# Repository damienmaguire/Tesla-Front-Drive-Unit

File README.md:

# Tesla-Front-Drive-Unit
Open Source Logic board to control the Tesla Model S Front Drive Unit
This board replaces the Tesla OEM control board in the high efficency front drive unit
and enables full control of the inverter and motor using simple analog / digital and CAN communication. Design files in DesignSpark 8 format.

Software may be downladed here:
https://github.com/jsphuebner/stm32-sine/releases

Fully built and tested boards and bare PCBs available here : http://www.evbmw.com/index.php/evbmw-webshop

Support forum : https://openinverter.org/forum/

23/09/17 : Released V1 schematic for the logic board. Untested. Also released pinout for the logic to igbt board interface header and Autocad dxf of the board outline with critical component locations.

02/10/17 : Released V1 design files. Untested. Unproven. Educational use only.

06/11/17 : V1 board bench tested and working well. No in car testing as yet.

29/12/17 : Uploaded V2 design files for small drive unit logic board. Compatible with both front and rear small Tesla drive units.

Just one change :

ULN2003 replaced by NCV8401ADT for driving precharge relay and main contactor following in car testing of the large drive unit.

Happy new year :)

14/08/18 : Following some excellent testing and investigation by a european customer, V3 design files are released. Small changes to component values in the current sensor opamp circuit as well as addition of two filter capacitors in the same. Now running well in vehicle. Also uploaded working parameter file.

18/10/18 : Two customers reported failures of their inverter when using the V2 board. One customer reported they had fixed the issue but then refused to share the details. I have worked with the second customer in Romania on the problems. Here are some details :

Root cause of the drive unit inverter failures discovered and fixed.
NOT caused by overcurrent through the igbts but rather the combination of using 8.8kHz switching frequency through a very low inductance stator and the sudden release of the main contactor on an overcurrent detection. The small drive unit inverter works perfectly at 17.6khz switching frequency and setting tripmode to prechon ensures the pre charge resistor can provide a path back to the battery during release of the main contactor. This was tested to the Nth degree on my recent trip to Romania

Working on a fix for a hardware bug that is limiting power. The tesla current sensors span +/- 1250A over a range of 0-5v with 2.5v representing 0A. Seems Tesla use the EXACT SAME hardware overcurrent detection circuit on their logic board as designed by Johannes. They set trip points at .1V and 4.9V giving a total span of 1200A. (1A=2mV). The component choice in the opamp circuit on the open source board causes a hardware overcurrent event at +850A regardless of settings above this value thus limiting power. It was this trip coupled with the above issues relating to main contactor control and switching frequency that lead to inverter deaths.

Identified the hall effect current sensor used in the small drive units as the MLX91209. So at least now if I wreck one they only cost 3 Euros to replace. A V4 design will be released shortly along with details on how to modify the V2 and V3 boards to avoid this problem. 

28/10/18 : V4 Design files released. Major changes : 

Updated current sensor opamp component values to allow the full +/-1200A swing.

Deleted the encoder polarity jumper as no longer needed.

Added option to fit ESP WiFi module on board (untested)

Added jumper to disable RS232 Transciever (required if using on board wifi)

Latest sourcecode and binaries will available from https://github.com/jsphuebner/stm32-sine

V2 and V3 boards can still be used by changing the following component values : R44,R49 = 62k, R48 = 3k16.

On the web interface set the following two parameters :

PWMFRQ=17.6kHz

Tripmode = Prechon

Working and tested full parameter files will be released shortly.

29/10/18 : V2 Design files and BOM updated for modifications and also incorrect values for temp sensor load resistors in BOM.

Test run with modification : https://www.youtube.com/watch?v=mhGwcPWCbsA

21/01/20 : V6 design files now released. Both fully built and partial built boards available from the EVBMW webshop : https://www.evbmw.com/index.php/evbmw-webshop
Don't want to buy from me and support ongoing development? That's ok as this release also includes the BOM, CPL and Gerber files needed to build your own at JLCPCB : https://jlcpcb.com

16/12/25 : Added current Kicad 9 project to redesign the SDU board. Work in progress.

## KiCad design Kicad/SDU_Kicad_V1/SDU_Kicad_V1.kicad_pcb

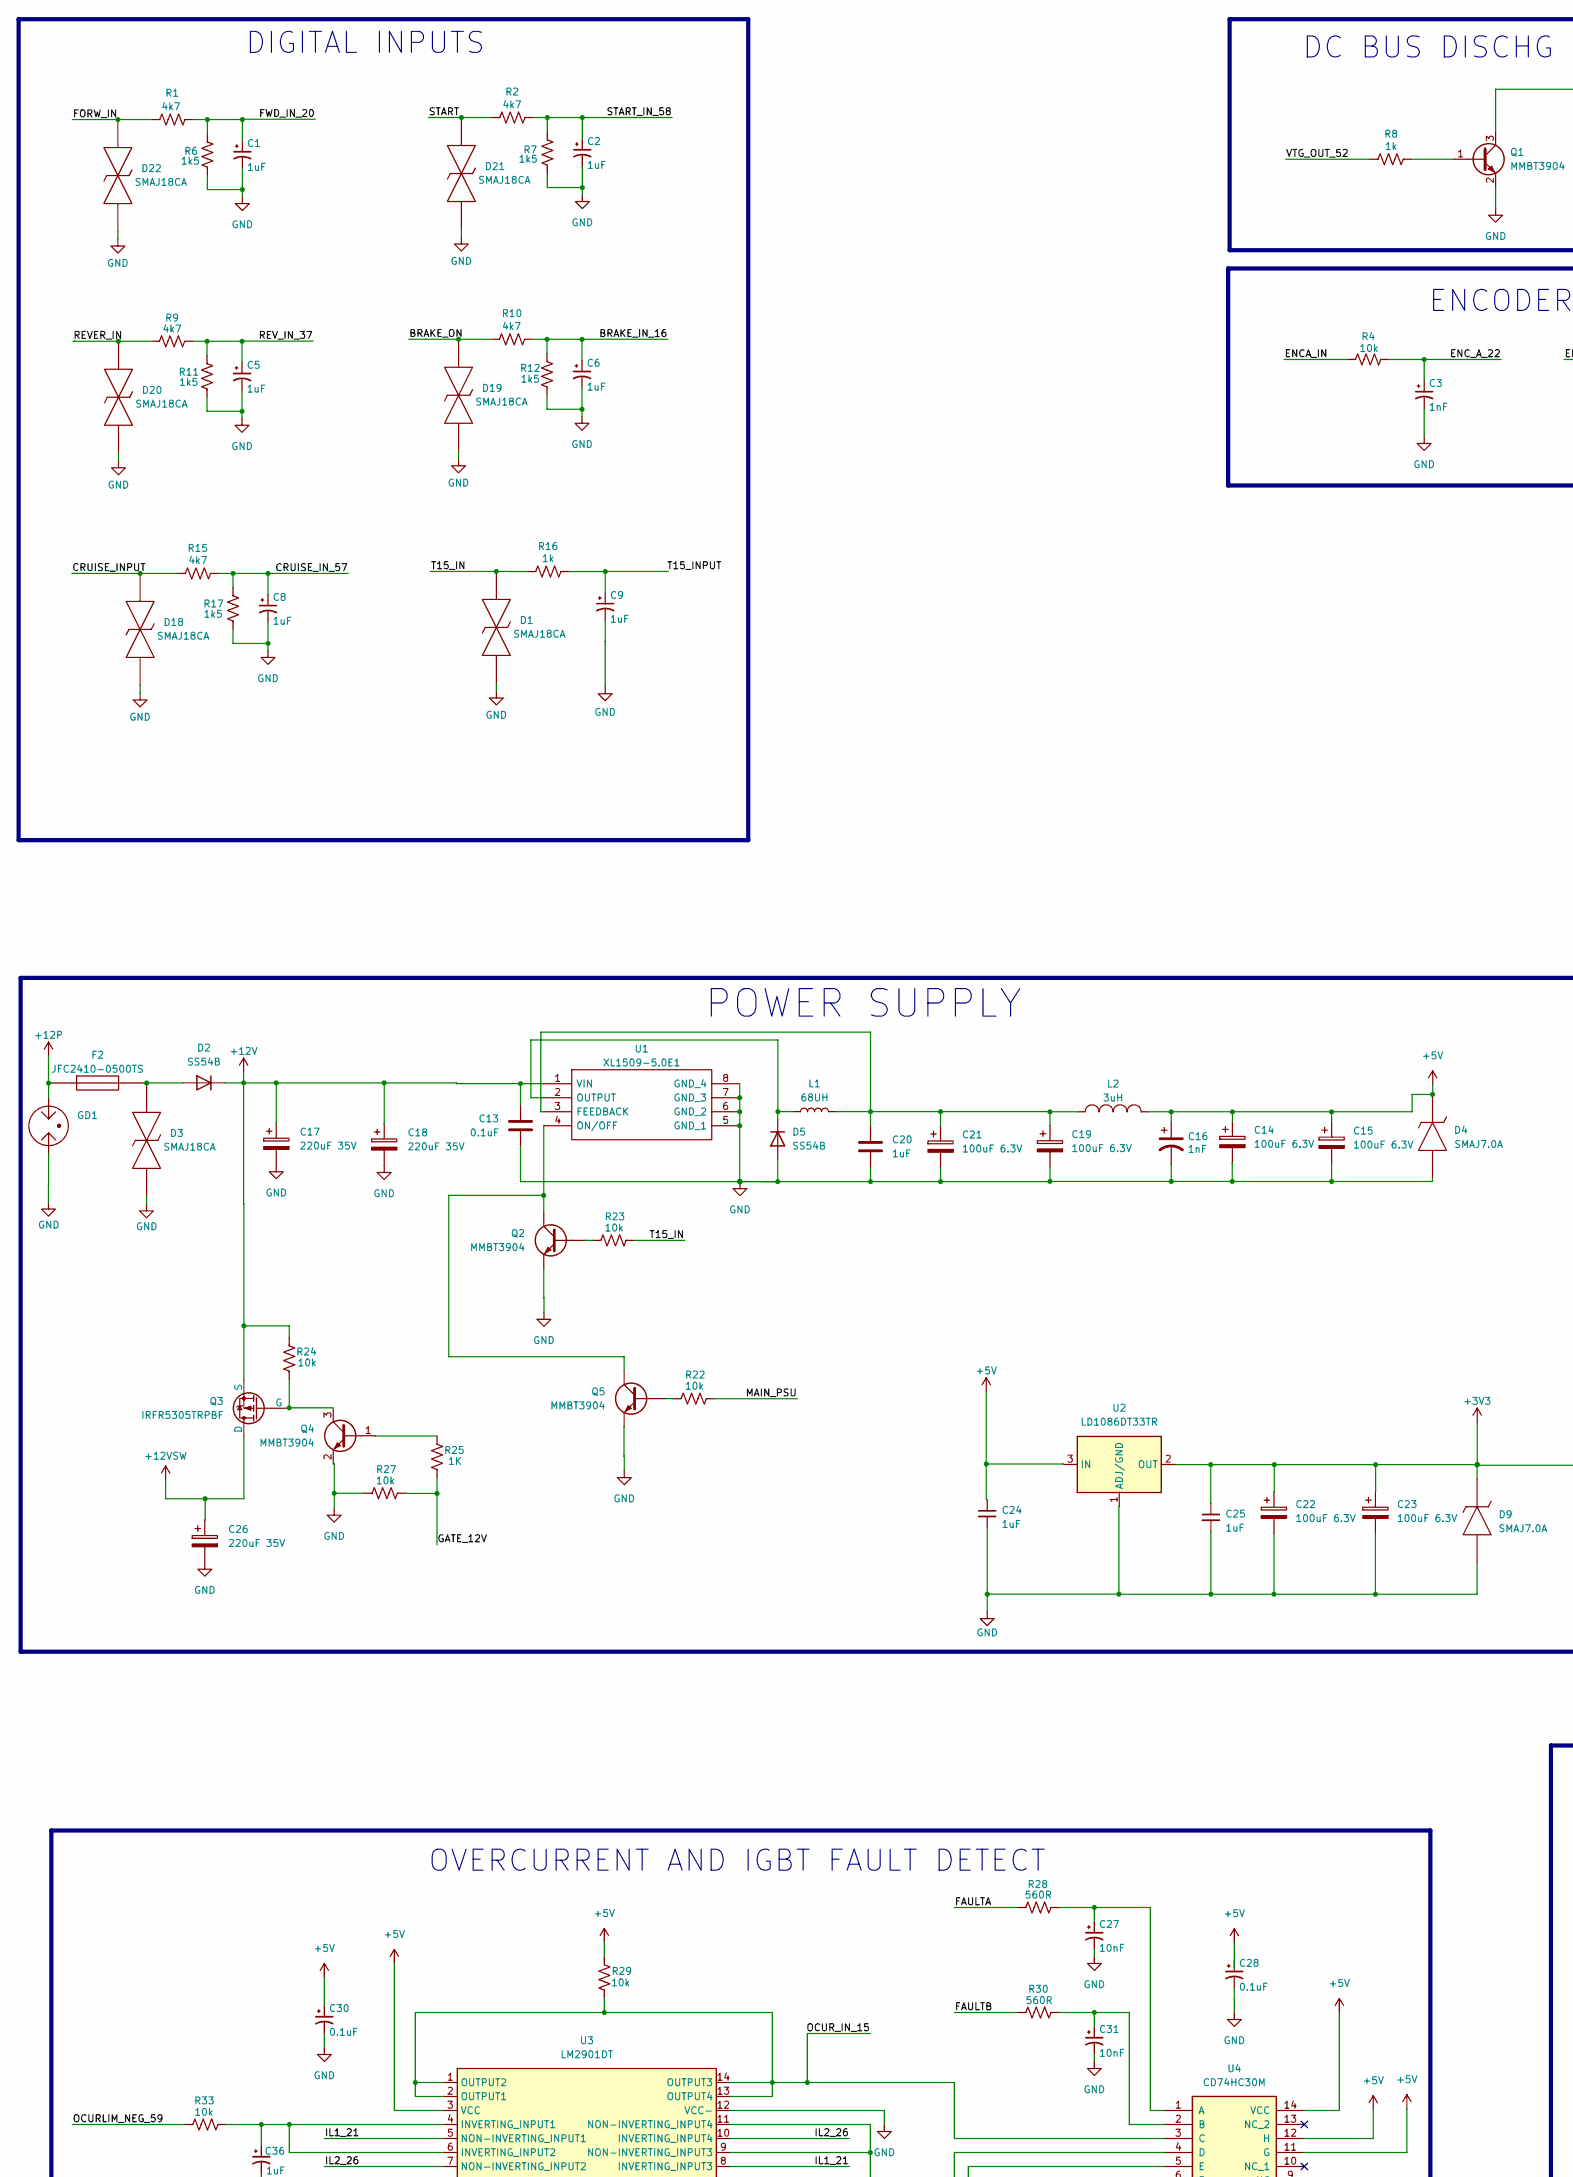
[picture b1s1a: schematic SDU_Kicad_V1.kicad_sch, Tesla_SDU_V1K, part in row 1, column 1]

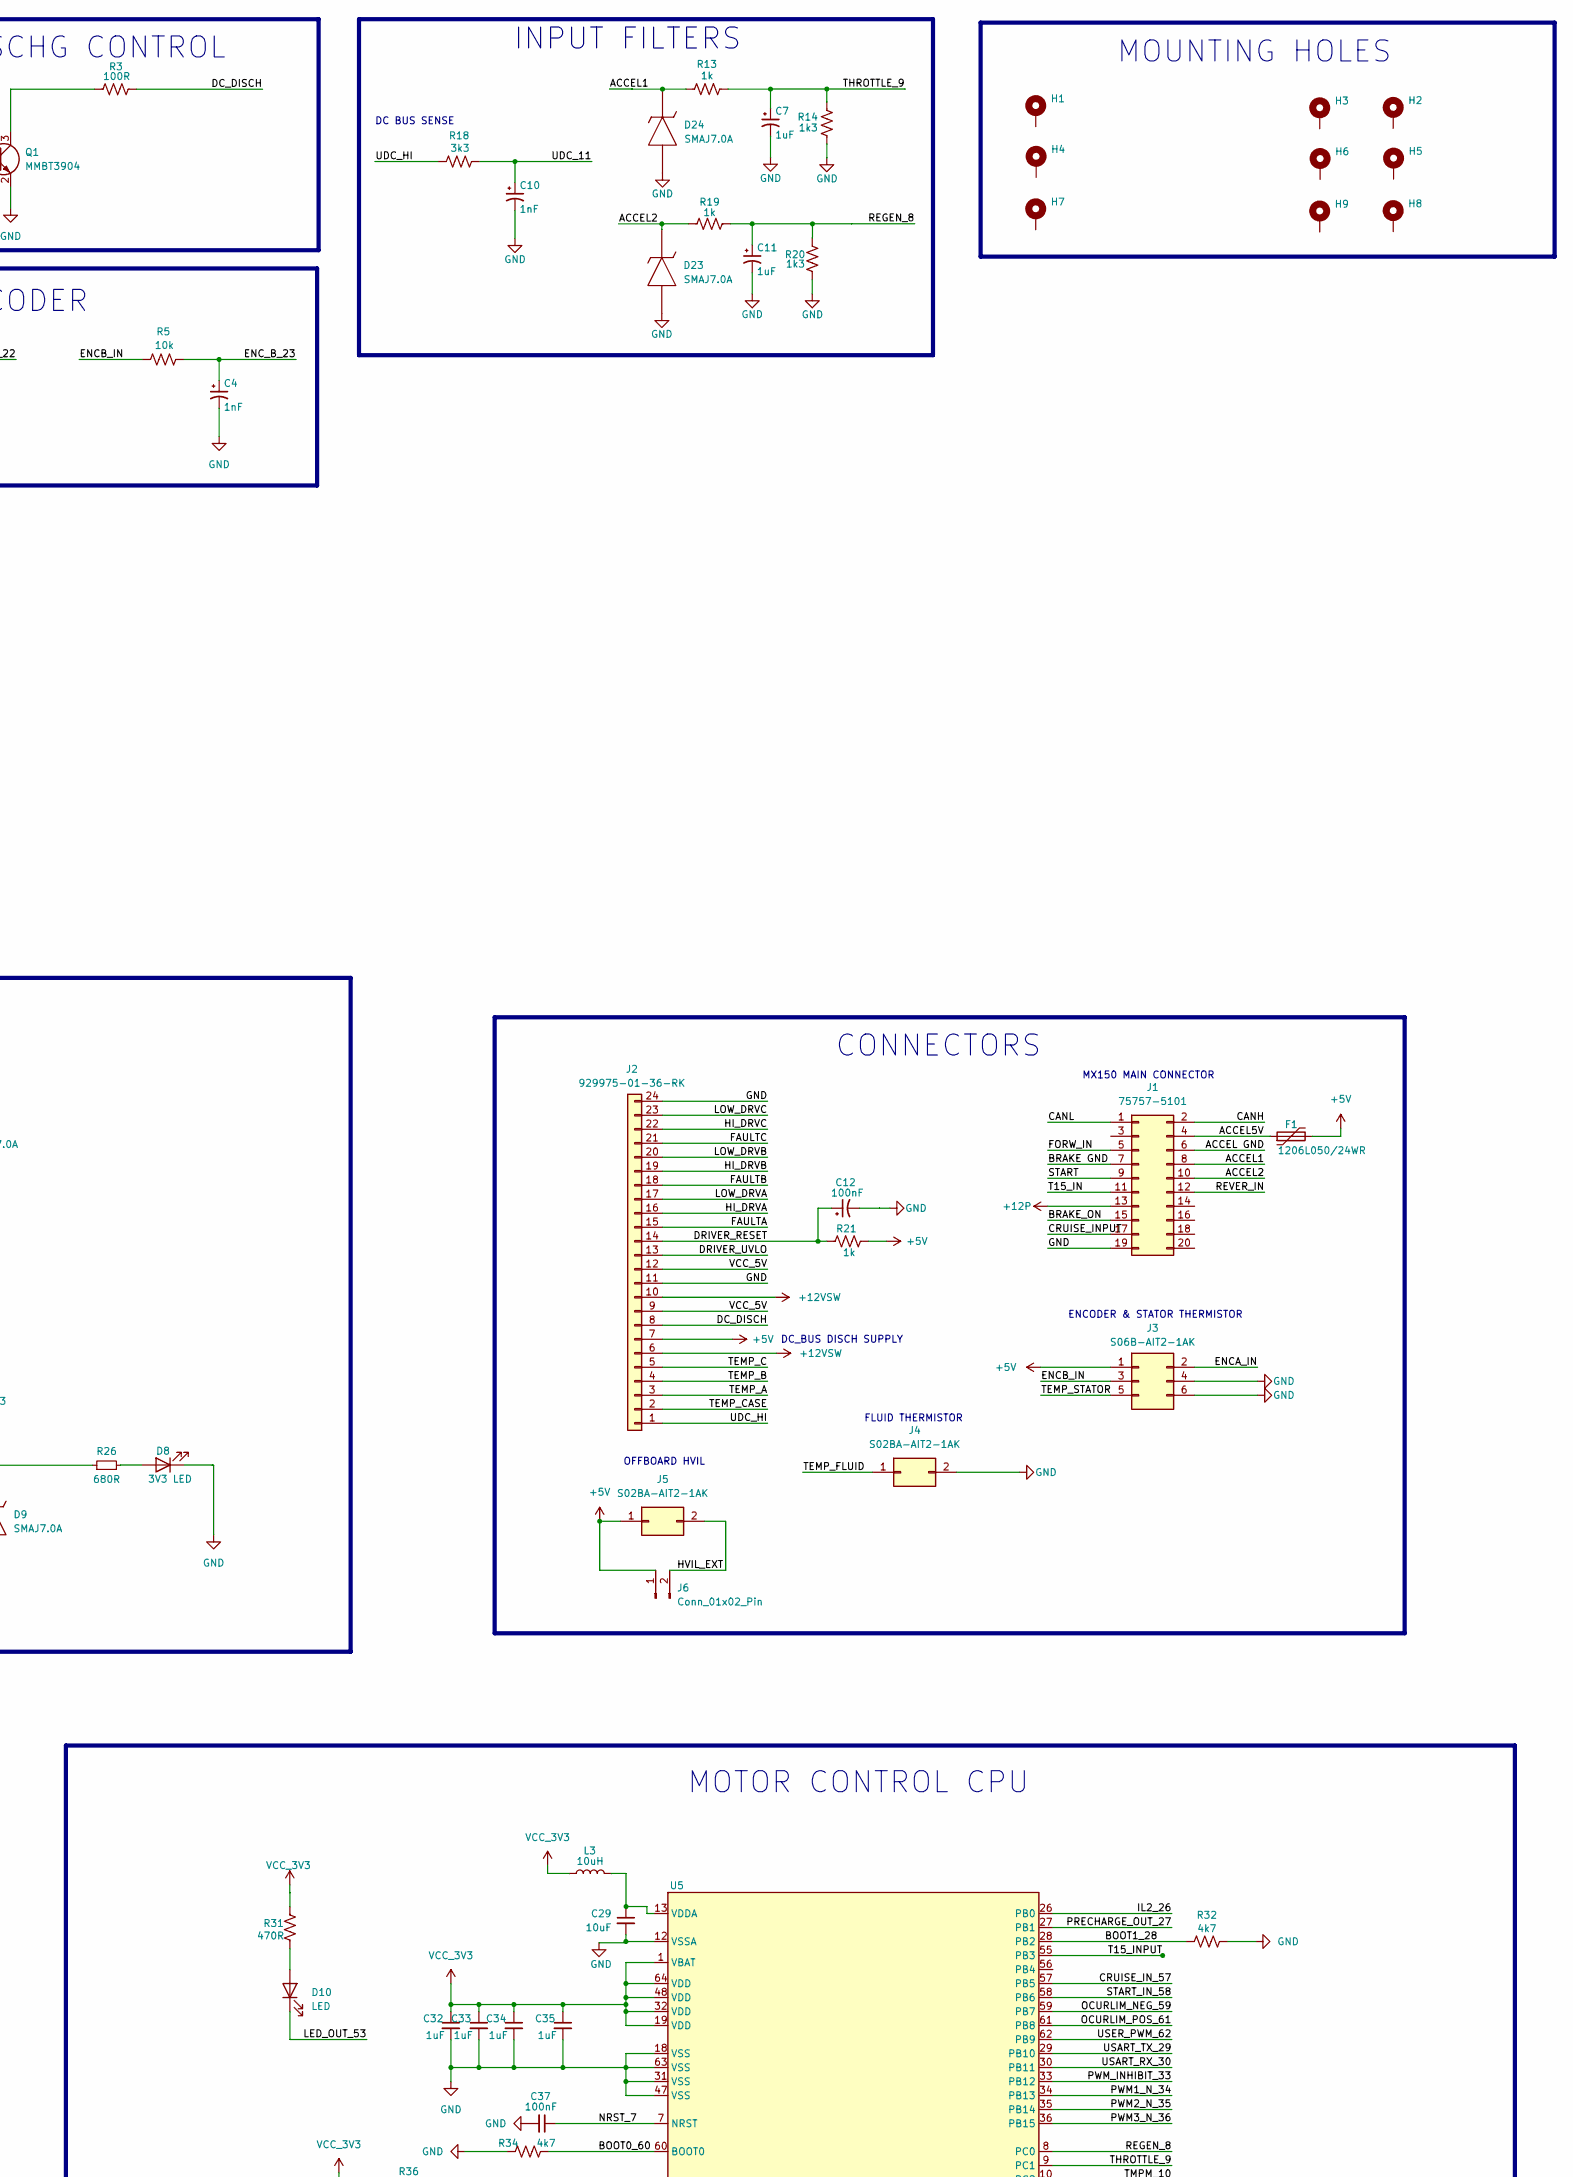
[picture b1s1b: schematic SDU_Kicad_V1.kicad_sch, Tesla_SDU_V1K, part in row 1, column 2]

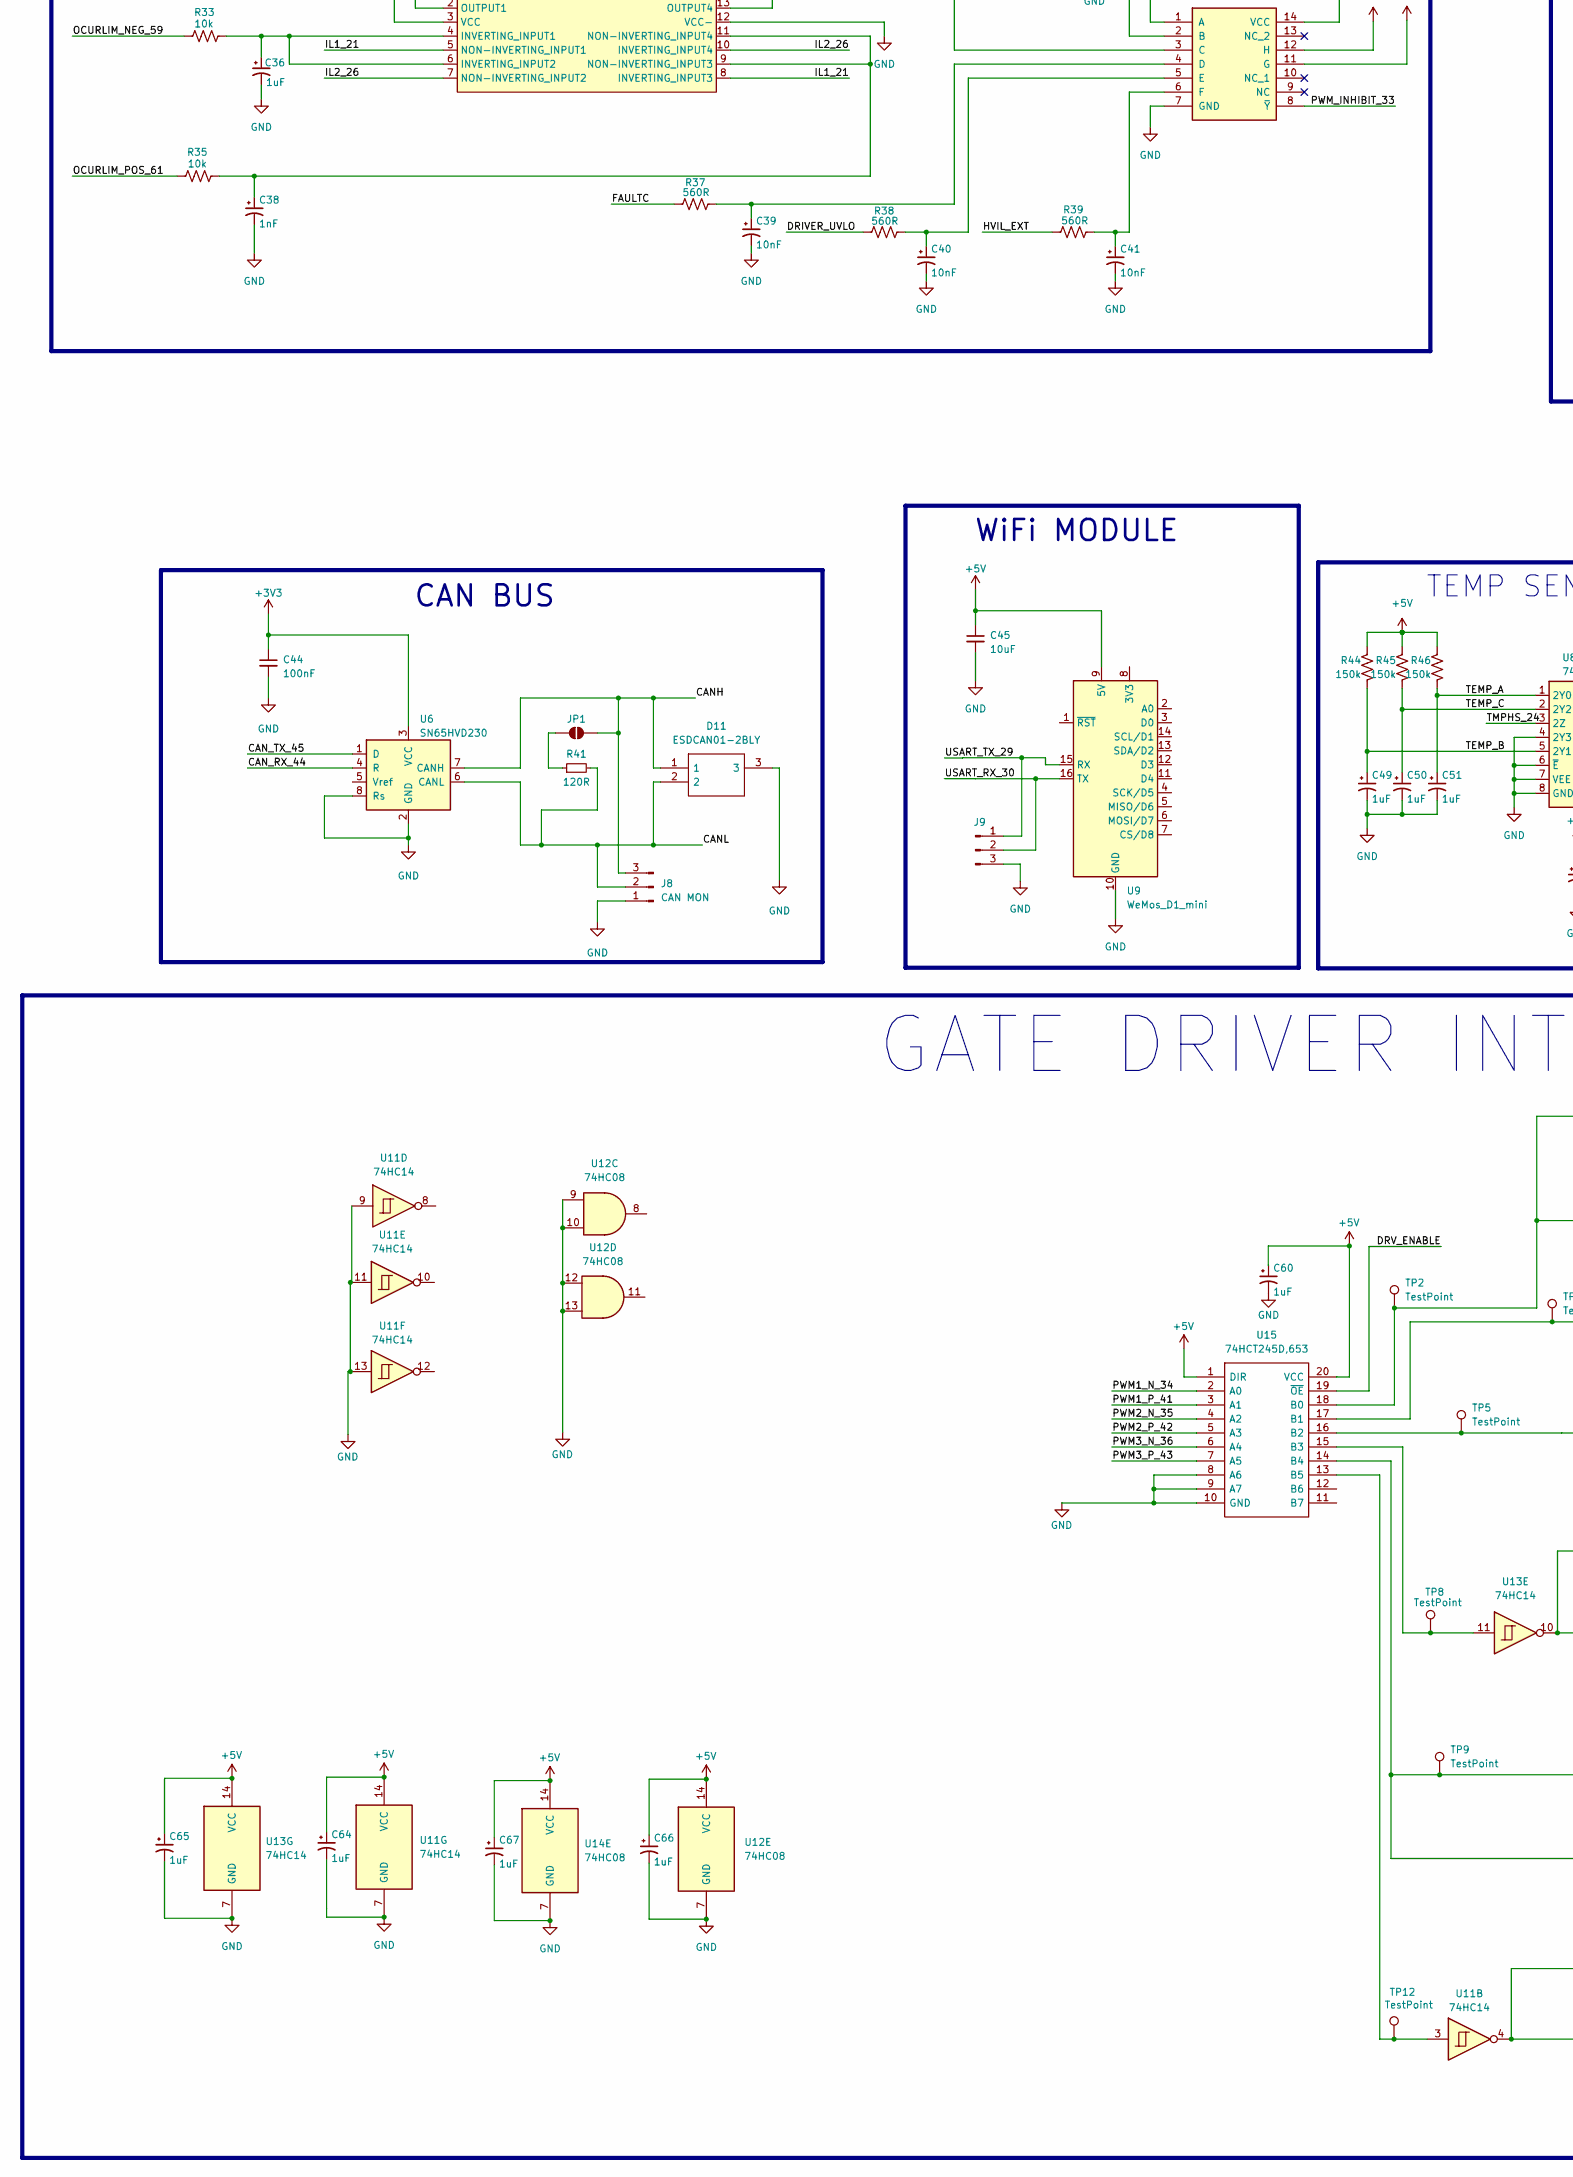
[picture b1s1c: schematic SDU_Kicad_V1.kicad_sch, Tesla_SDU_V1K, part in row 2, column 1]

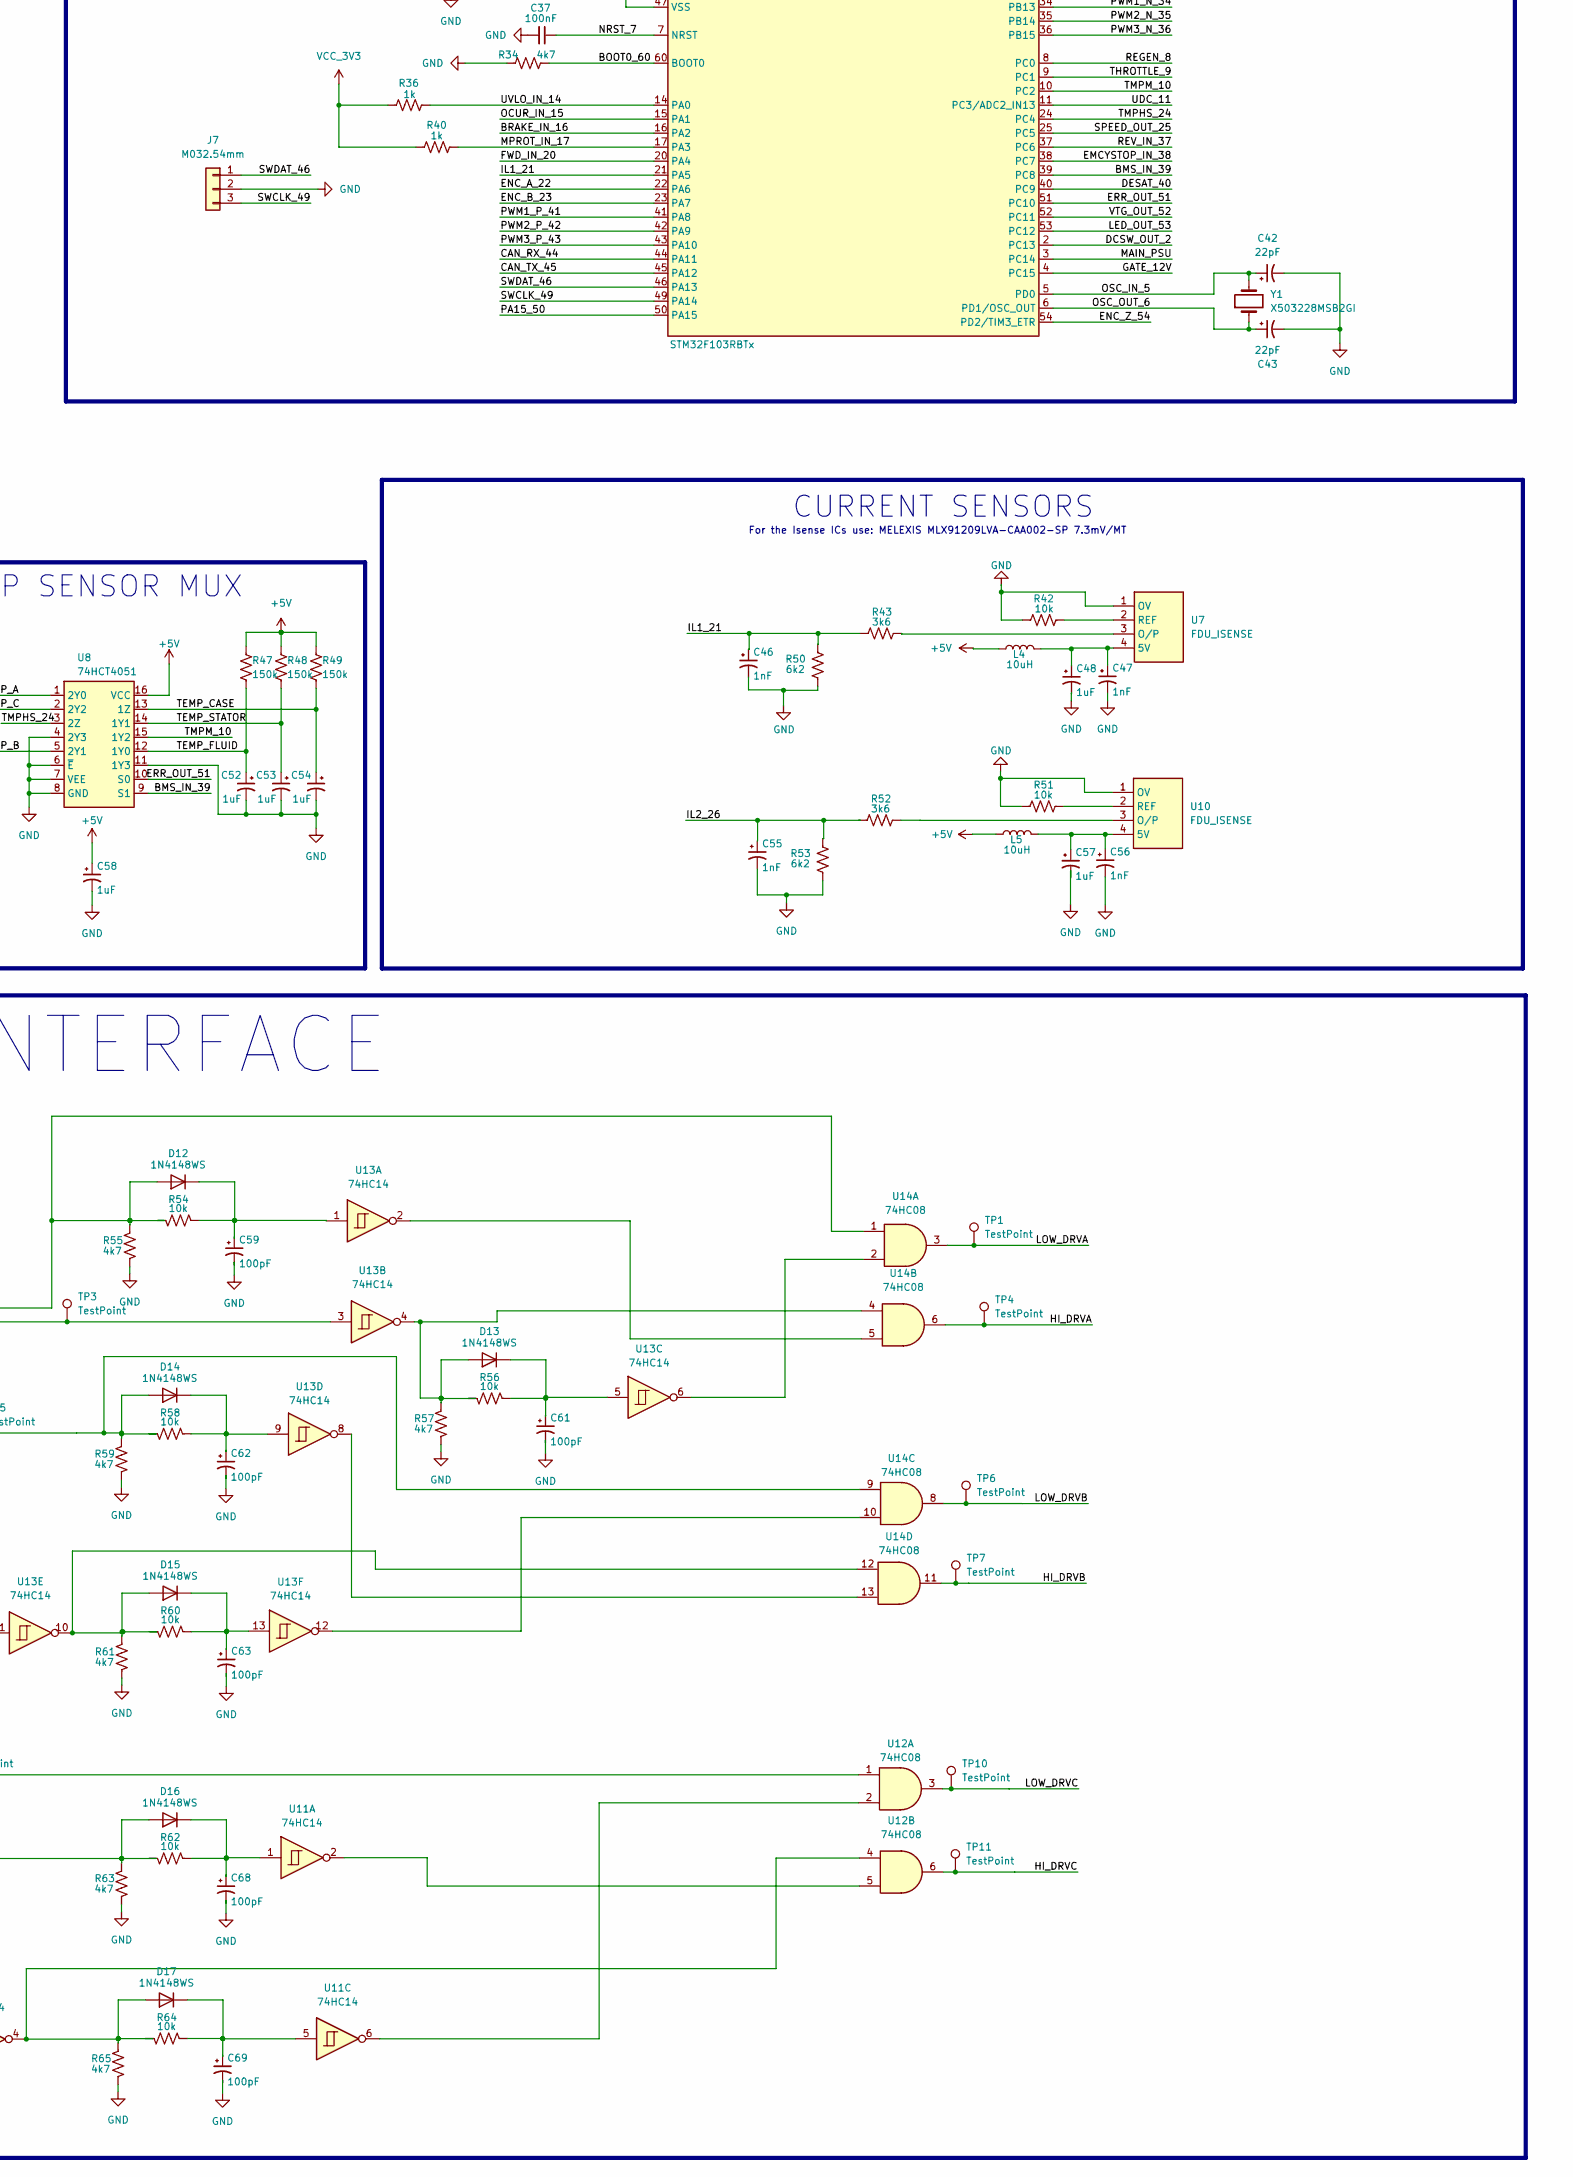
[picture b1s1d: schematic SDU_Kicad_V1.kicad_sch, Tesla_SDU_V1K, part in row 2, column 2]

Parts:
C1, C2, C5, C6, C7, C8, C9, C11, C20, C24, C25, C32, C33, C34, C35, C36, C48, C49, C50, C51, C52, C53, C54, C57, C58, C60, C64, C65, C66, C67: 1uF; C_0805_2012Metric
C3, C4, C10, C16, C38, C46, C47, C55, C56: 1nF; C_0805_2012Metric
C12, C37, C44: 100nF; C_0805_2012Metric
C13, C28, C30: 0.1uF; C_0805_2012Metric
C14, C15, C19, C21, C22, C23: 100uF 6.3V; CP_EIA-3528-15_AVX-H
C17, C18, C26: 220uF 35V; CP_Elec_10x10
C27, C31, C39, C40, C41: 10nF; C_0805_2012Metric
C29, C45: 10uF; C_0805_2012Metric
C42, C43: 22pF; C_0805_2012Metric
C59, C61, C62, C63, C68, C69: 100pF; C_0805_2012Metric
D1, D3, D18, D19, D20, D21, D22: SMAJ18CA; DIONM5127X229N; Manufacturer_Part_Number SMAJ18CA; Mouser Part Number 652-SMAJ18CA
D2, D5: SS54B; D_SMA
D4, D9: SMAJ7.0A; DIOM5026X229N; Manufacturer_Part_Number SMAJ7.0A; Mouser Part Number 576-SMAJ7.0A
D8: 3V3 LED; LED_0805_2012Metric
D10: LED; LED_0805_2012Metric
D11: ESDCAN01-2BLY; SOT95P255X150-3N; Manufacturer_Part_Number ESDCAN01-2BLY; Mouser Part Number 511-ESDCAN01-2BLY
D12, D13, D14, D15, D16, D17: 1N4148WS; D_SOD-323
D23, D24: SMAJ7.0A; DIONM5127X229N; Manufacturer_Part_Number SMAJ7.0A; Mouser Part Number 576-SMAJ7.0A
F1: 1206L050/24WR; Fuse_1206_3216Metric
F2: JFC2410-0500TS; FUSC6126X280N; Manufacturer_Part_Number JFC2410-0500TS
GD1: 2051-09-SM-RPLF; DIOM5336X244N
H1, H4, H7: MountingHole_Pad; MountingHole_5.3mm_M5_Pad_Via
H2, H3, H5, H6, H8, H9: MountingHole_Pad; MountingHole_3.2mm_M3_Pad_Via
J1: 75757-5101; SDU_Conn
J2: 929975-01-36-RK; SDU_IGBT_Conn
J3: S06B-AIT2-1AK; 6pin_JST
J4, J5: S02BA-AIT2-1AK; 2pin_JST
J6: Conn_01x02_Pin; PinHeader_2x01_P2.54mm_Horizontal
J7: M032.54mm; PinSocket_1x03_P2.54mm_Vertical
J8: CAN MON; PinHeader_1x03_P2.54mm_Vertical
J9: Conn_01x03_Pin; PinHeader_1x03_P2.54mm_Vertical
JP1: SolderJumper_2_Open; SolderJumper-2_P1.3mm_Open_Pad1.0x1.5mm
L1: 68UH; L_Sumida_CDMC6D28_7.25x6.5mm
L2: 3uH; L_APV_ANR6020
L3, L4, L5: 10uH; L_0805_2012Metric
Q1, Q2, Q4, Q5: MMBT3904; SOT-23
Q3: IRFR5305TRPBF; TO-252-2
R1, R2, R9, R10, R15, R32, R34, R55, R57, R59, R61, R63, R65: 4k7; R_0805_2012Metric
R3: 100R; R_0805_2012Metric
R4, R5, R22, R23, R24, R27, R29, R33, R35, R42, R51, R54, R56, R58, R60, R62, R64: 10k; R_0805_2012Metric
R6, R7, R11, R12, R17: 1k5; R_0805_2012Metric
R8, R13, R16, R19, R21, R36, R40: 1k; R_0805_2012Metric
R14, R20: 1k3; R_0805_2012Metric
R18: 3k3; R_0805_2012Metric
R25: 1K; R_0805_2012Metric
R26: 680R; R_0805_2012Metric
R28, R30, R37, R38, R39: 560R; R_0805_2012Metric
R31: 470R; R_0805_2012Metric
R41: 120R; R_0805_2012Metric
R43, R52: 3k6; R_0805_2012Metric
R44, R45, R46, R47, R48, R49: 150k; R_0805_2012Metric
R50, R53: 6k2; R_0805_2012Metric
TP1, TP2, TP3, TP4, TP5, TP6, TP7, TP8, TP9, TP10, TP11, TP12: TestPoint; TestPoint_Pad_2.5x2.5mm
U1: XL1509-5.0E1; SOIC127P600X175-8N; Manufacturer_Part_Number XL1509-5.0E1
U2: LD1086DT33TR; TO-252-2
U3: LM2901DT; SOIC-14_3.9x8.7mm_P1.27mm
U4: CD74HC30M; SOIC-14_3.9x8.7mm_P1.27mm
U5: STM32F103RBTx; LQFP-64_10x10mm_P0.5mm
U6: SN65HVD230; SOIC-8_3.9x4.9mm_P1.27mm
U7, U10: FDU_ISENSE; SDU_Isens
U8: 74HCT4051; SOIC-16_3.9x9.9mm_P1.27mm
U9: WeMos_D1_mini; WEMOS_D1_mini_light
U11, U13: 74HC14; TSSOP-14_4.4x5mm_P0.65mm
U12, U14: 74HC08; SOIC-14_3.9x8.7mm_P1.27mm
U15: 74HCT245D,653; SOIC127P1032X265-20N; Manufacturer_Part_Number 74HCT245D,653; Mouser Part Number 771-74HCT245D-T
Y1: X503228MSB2GI; Crystal_SMD_5032-2Pin_5.0x3.2mm

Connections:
+3V3: C22.1, C23.1, C25.1, C44.1, D9.1, R26.1, U2.2 (OUT), U6.3 (VCC)
+5V: C14.1, C15.1, C16.1, C24.1, C28.1, C30.1, C45.1, C58.1, C60.1, C64.1, C65.1, C66.1, C67.1, D4.1, F1.2, J2.7, J3.1, J5.1, J6.1, L2.2, L4.1, L5.1, R21.1, R29.2, R44.1, R45.1, R46.1, R47.1, R48.1, R49.1, U2.3 (IN), U3.3 (VCC), U4.11 (G), U4.12 (H), U4.14 (VCC), U8.16 (VCC), U9.9 (5V), U11.14 (VCC), U12.14 (VCC), U13.14 (VCC), U14.14 (VCC), U15.1 (DIR), U15.20 (VCC)
+12P: F2.1, GD1.2, J1.13
+12V: C13.1, C17.1, C18.1, D2.1 (K), Q3.3 (S), R24.1, U1.1 (VIN)
+12VSW: C26.1, J2.6, J2.10, Q3.1 (D)
/ACCEL1: D24.1, J1.8, R13.1
/ACCEL2: D23.1, J1.10, R19.1
/ACCEL5V: F1.1, J1.4
/ACCEL GND: J1.6
/BMS_IN_39: U5.39 (PC8), U8.9 (S1)
/BOOT0_60: R34.2, U5.60 (BOOT0)
/BOOT1_28: R32.1, U5.28 (PB2)
/BRAKE GND: J1.7
/BRAKE_IN_16: C6.1, R10.2, R12.2, U5.16 (PA2)
/BRAKE_ON: D19.1, J1.15, R10.1
/CANH: D11.1, J1.2, J8.3, JP1.2 (B), U6.7 (CANH)
/CANL: D11.2, J1.1, J8.2, R41.2, U6.6 (CANL)
/CAN_RX_44: U5.44 (PA11), U6.4 (R)
/CAN_TX_45: U5.45 (PA12), U6.1 (D)
/CRUISE_INPUT: D18.1, J1.17, R15.1
/CRUISE_IN_57: C8.1, R15.2, R17.2, U5.57 (PB5)
/DCSW_OUT_2: U5.2 (PC13)
/DC_DISCH: J2.8, R3.2
/DESAT_40: U5.40 (PC9)
/DRIVER_RESET: C12.1, J2.14, R21.2
/DRIVER_UVLO: J2.13, R38.1
/DRV_ENABLE: U15.19 (~OE)
/EMCYSTOP_IN_38: U5.38 (PC7)
/ENCA_IN: J3.2, R4.1
/ENCB_IN: J3.3, R5.1
/ENC_A_22: C3.1, R4.2, U5.22 (PA6)
/ENC_B_23: C4.1, R5.2, U5.23 (PA7)
/ENC_Z_54: U5.54 (PD2/TIM3_ETR)
/ERR_OUT_51: U5.51 (PC10), U8.10 (S0)
/FAULTA: J2.15, R28.1
/FAULTB: J2.18, R30.1
/FAULTC: J2.21, R37.1
/FORW_IN: D22.1, J1.5, R1.1
/FWD_IN_20: C1.1, R1.2, R6.2, U5.20 (PA4)
/GATE_12V: R25.2, R27.2, U5.4 (PC15)
/HI_DRVA: J2.16, TP4.1, U14.6
/HI_DRVB: J2.19, TP7.1, U14.11
/HI_DRVC: J2.22, TP11.1, U12.6
/HVIL_EXT: J5.2, J6.2, R39.1
/IL1_21: C46.1, R43.1, R50.2, U3.5 (NON-INVERTING_INPUT1), U3.8 (INVERTING_INPUT3), U5.21 (PA5)
/IL2_26: C55.1, R52.1, R53.2, U3.7 (NON-INVERTING_INPUT2), U3.10 (INVERTING_INPUT4), U5.26 (PB0)
/LED_OUT_53: D10.1 (K), U5.53 (PC12)
/LOW_DRVA: J2.17, TP1.1, U14.3
/LOW_DRVB: J2.20, TP6.1, U14.8
/LOW_DRVC: J2.23, TP10.1, U12.3
/MPROT_IN_17: R40.2, U5.17 (PA3)
/NRST_7: C37.1, U5.7 (NRST)
/OCURLIM_NEG_59: R33.1, U5.59 (PB7)
/OCURLIM_POS_61: R35.1, U5.61 (PB8)
/OCUR_IN_15: R29.1, U3.1 (OUTPUT2), U3.2 (OUTPUT1), U3.13 (OUTPUT4), U3.14 (OUTPUT3), U4.3 (C), U5.15 (PA1)
/OSC_IN_5: C42.1, U5.5 (PD0), Y1.2
/OSC_OUT_6: C43.1, U5.6 (PD1/OSC_OUT), Y1.1
/PA15_50: U5.50 (PA15)
/PRECHARGE_OUT_27: U5.27 (PB1)
/PWM1_N_34: U5.34 (PB13), U15.2 (A0)
/PWM1_P_41: U5.41 (PA8), U15.3 (A1)
/PWM2_N_35: U5.35 (PB14), U15.4 (A2)
/PWM2_P_42: U5.42 (PA9), U15.5 (A3)
/PWM3_N_36: U5.36 (PB15), U15.6 (A4)
/PWM3_P_43: U5.43 (PA10), U15.7 (A5)
/PWM_INHIBIT_33: U4.8 (~Y), U5.33 (PB12)
/REGEN_8: C11.1, R19.2, R20.2, U5.8 (PC0)
/REVER_IN: D20.1, J1.12, R9.1
/REV_IN_37: C5.1, R9.2, R11.2, U5.37 (PC6)
/SPEED_OUT_25: U5.25 (PC5)
/START: D21.1, J1.9, R2.1
/START_IN_58: C2.1, R2.2, R7.2, U5.58 (PB6)
/SWCLK_49: J7.3, U5.49 (PA14)
/SWDAT_46: J7.1, U5.46 (PA13)
/T15_INPUT: C9.1, R16.2, U5.55 (PB3)
/TEMP_A: C51.1, J2.3, R46.2, U8.1 (2Y0)
/TEMP_B: C49.1, J2.4, R44.2, U8.5 (2Y1)
/TEMP_C: C50.1, J2.5, R45.2, U8.2 (2Y2)
/TEMP_CASE: C54.1, J2.2, R49.2, U8.13 (1Z)
/TEMP_FLUID: C52.1, J4.1, R47.2, U8.12 (1Y0)
/TEMP_STATOR: C53.1, J3.5, R48.2, U8.14 (1Y1)
/THROTTLE_9: C7.1, R13.2, R14.2, U5.9 (PC1)
/TMPHS_24: U5.24 (PC4), U8.3 (2Z)
/TMPM_10: U5.10 (PC2), U8.15 (1Y2)
/UDC_11: C10.1, R18.2, U5.11 (PC3/ADC2_IN13)
/UDC_HI: J2.1, R18.1
/USART_RX_30: J9.2, U5.30 (PB11), U9.16 (TX)
/USART_TX_29: J9.1, U5.29 (PB10), U9.15 (RX)
/USER_PWM_62: U5.62 (PB9)
/UVLO_IN_14: R36.2, U5.14 (PA0)
/VCC_5V: J2.9, J2.12
/VTG_OUT_52: R8.1, U5.52 (PC11)
unnamed: D2.2 (A), D3.1, F2.2
unnamed: D5.1 (K), L1.1, U1.2 (OUTPUT)
unnamed: D8.2 (A), R26.2
unnamed: D10.2 (A), R31.1
unnamed: D12.2 (A), R54.2, R55.2, TP2.1, U14.1, U15.18 (B0)
unnamed: C59.1, D12.1 (K), R54.1, U13.1
unnamed: D13.2 (A), R56.2, R57.2, U13.4, U14.4
unnamed: C61.1, D13.1 (K), R56.1, U13.5
unnamed: D14.2 (A), R58.2, R59.2, TP5.1, U14.9, U15.16 (B2)
unnamed: C62.1, D14.1 (K), R58.1, U13.9
unnamed: D15.2 (A), R60.2, R61.2, U13.10, U14.12
unnamed: C63.1, D15.1 (K), R60.1, U13.13
unnamed: D16.2 (A), R62.2, R63.2, TP9.1, U12.1, U15.14 (B4)
unnamed: C68.1, D16.1 (K), R62.1, U11.1
unnamed: D17.2 (A), R64.2, R65.2, U11.4, U12.4
unnamed: C69.1, D17.1 (K), R64.1, U11.5
unnamed: JP1.1 (A), R41.1
unnamed: Q1.1 (B), R8.2
unnamed: Q1.3 (C), R3.1
unnamed: Q2.3 (C), Q5.3 (C), U1.4 (ON/OFF)
unnamed: Q3.2 (G), Q4.3 (C), R24.2
unnamed: Q4.1 (B), R25.1
unnamed: C19.1, C20.1, C21.1, L1.2, L2.1, U1.3 (FEEDBACK)
unnamed: C36.1, R33.2, U3.4 (INVERTING_INPUT1), U3.6 (INVERTING_INPUT2)
unnamed: C38.1, R35.2, U3.9 (NON-INVERTING_INPUT3), U3.11 (NON-INVERTING_INPUT4)
unnamed: C27.1, R28.2, U4.1 (A)
unnamed: C31.1, R30.2, U4.2 (B)
unnamed: C39.1, R37.2, U4.4 (D)
unnamed: C40.1, R38.2, U4.5 (E)
unnamed: C41.1, R39.2, U4.6 (F)
unnamed: C29.1, L3.2, U5.13 (VDDA)
unnamed: C47.1, C48.1, L4.2, U7.4 (5V)
unnamed: R43.2, U7.3 (O/P)
unnamed: R42.2, U7.2 (REF)
unnamed: C56.1, C57.1, L5.2, U10.4 (5V)
unnamed: R52.2, U10.3 (O/P)
unnamed: R51.2, U10.2 (REF)
unnamed: U11.2, U12.5
unnamed: U11.6, U12.2
unnamed: U13.2, U14.5
unnamed: U13.6, U14.2
unnamed: U13.8, U14.13
unnamed: U13.12, U14.10
unnamed: TP3.1, U13.3, U15.17 (B1)
unnamed: TP8.1, U13.11, U15.15 (B3)
unnamed: TP12.1, U11.3, U15.13 (B5)
VCC_3V3: C32.1, C33.1, C34.1, C35.1, L3.1, R31.2, R36.1, R40.1, U5.1 (VBAT), U5.19 (VDD), U5.32 (VDD), U5.48 (VDD), U5.64 (VDD)

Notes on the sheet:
MOTOR CONTROL CPU
FLUID THERMISTOR
MX150 MAIN CONNECTOR
OVERCURRENT AND IGBT FAULT DETECT
TEMP SENSOR MUX
DC_BUS DISCH SUPPLY
DIGITAL INPUTS
GATE DRIVER INTERFACE
POWER SUPPLY
MOUNTING HOLES
CURRENT SENSORS
ENCODER
WiFi MODULE
CONNECTORS
CAN BUS
DC BUS DISCHG CONTROL
INPUT FILTERS
DC BUS SENSE
For the Isense ICs use: MELEXIS MLX91209LVA-CAA002-SP 7.3mV/MT
OFFBOARD HVIL
ENCODER & STATOR THERMISTOR

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
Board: 4 copper layers, 217 parts (2 on the bottom side), 133 nets, no tracks yet.

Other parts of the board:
D6, D7: 1N4148WS; D_SOD-323

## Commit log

2017-09-22 Add files via upload
    Autocad dxf file of board outline , hole positions and connectors for the Tesla front drive unit PCB.
2021-10-07 Update Tesla_FDU_V6_BOM_JLC.xls
    Updated "Package" header to "Footprint" for compatibility with JLCPCB's recent SMT quoting changes
2025-11-16 Add Kicad project

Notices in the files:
Kicad/SDU_Kicad_V1/SDU_Kicad_V1.kicad_pcb:
COPYRIGHT 2025
